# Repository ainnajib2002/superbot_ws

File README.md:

# 🛒 Semi-Autonomous Mobile Robot for Supermarket Shopping Efficiency

## 📌 Abstract
The rapid advancement of robotics has driven the emergence of innovative solutions to enhance the convenience and efficiency of supermarket shopping. This study presents the design of a prototype semi-autonomous mobile supermarket robot that integrates autonomous navigation, precise motor control, and intuitive human–robot interaction based on human following and hand gestures. The robot employs a configuration of two omnidirectional wheels and a caster wheel for balance, driven by PG45 DC motors controlled by an ESP32 microcontroller with a BTS7960 driver. A PI control system with parameters Kp = 0.1 and Ki = 0.004 maintains motor speed with a steady-state error below 5% and without significant overshoot, both under no-load and load conditions up to 30 kg. For navigation, the robot is equipped with an RPLiDAR A2 sensor, odometry, and mapping based on the SLAM Toolbox. Path planning is implemented using the A-Star algorithm and the Dynamic Window Approach (DWA). Experimental results demonstrate that the robot successfully completes multi-point navigation and avoids both static and dynamic obstacles, with an average response time of 3.51–6.52 seconds. Beyond navigation, the robot enables natural human interaction through an RGB camera processed with the YOLOv11-Pose deep learning model, achieving an F1-score above 0.92 and inference speed of 14 FPS. Distance estimation is performed using triangulation of head–neck keypoints, yielding an average accuracy of MAPE 5.3%. Hand gesture detection demonstrates high reliability with confidence scores above 0.83 at distances of 1.5–5 meters, allowing users to flexibly activate human-following mode or stop the robot. Tests conducted in a supermarket-like simulation environment confirm that the robot can stably follow users, maneuver in narrow aisles, and adaptively switch between operating modes. By combining precise motor control, SLAM-based navigation, and gesture-based interaction, this supermarket robot prototype shows strong potential as an intelligent solution to support a more ergonomic, efficient, and adaptive shopping experience. The perception system includes:

- **RGB Camera** → YOLOv11-Pose for human detection, pose estimation, and hand gesture recognition.
- **LiDAR (RPLiDAR A2)** → 2D mapping and obstacle detection.
- **Odometry (wheel encoders)** → position estimation.
- **Load Cell** → payload weight monitoring.

The navigation system uses **SLAM Toolbox** for mapping, **AMCL** for localization, and **Nav2** (A* for global path, DWA for local planner).

---

## ⚙️ System Architecture
The system is divided into modules connected via ROS 2 topics and services:

- **Perception**: RGB Camera + YOLOv11-Pose, LiDAR, Odometry.
- **Control**: Differential drive with omnidirectional wheels, ESP32 motor control, Load cell feedback.
- **Navigation**: SLAM Toolbox, AMCL, Nav2 (A*, DWA).
- **GUI**: Tkinter-based interface for product categories, teleoperation, and visualization in RViz.

---

## 🖼️ System 

### 🔧 Wheel System
|  |  |
|------------------------------------------------------------|----------------------------------------------------------------|

### 🗺️ Mapping & SLAM
|  |  |
|------------------------------------------------------------|----------------------------------------------------------------|

### 🖥️ GUI Interface & Gesture
|  |  |
|------------------------------------------------------------|----------------------------------------------------------------|

### 👀 Human Detection 
|  |  |
|-------------------------------------------------------------------------------------------------------------|------------------------------------------------------------------------------------------------------------------|

---

## 🎯 Methods

### 1. Hardware
- **Jetson Orin Nano / Xavier NX** → AI inference & high-level computation.
- **ESP32** → Low-level motor control, encoder feedback, load cell data.
- **DC Motors + Omnidirectional wheels** → Maneuverability in narrow aisles.
- **RPLiDAR A2** → 360° scanning.
- **RGB Camera** → Human & gesture detection.
- **Load Cell** → Payload monitoring.

### 2. Perception (YOLOv11-Pose)
- Detects **human**, **keypoints (head–neck)** for distance estimation, and **hand gestures**.
- Custom dataset: 6,650 images, classes = {person, rock, paper, scissors}.
- Training with transfer learning → converted to TensorRT engine for Jetson.
- FPS ≈ 14, F1-score ≈ 0.92.

### 3. Human Following & Gesture Control
- Hybrid tracking with **AprilTag + YOLOv11-Pose + Kalman Filter**.
- Distance estimation via vertical keypoint distance (head–neck triangulation).
- Hand gestures mapped to robot commands:
  - **Rock (✊)** → STOP
  - **Paper (✋)** → HUMAN FOLLOW
  - **Scissors (✌️)** → GO

### 4. Navigation
- **Mapping**: SLAM Toolbox (multi-session mapping, pose graph optimization).
- **Localization**: AMCL with adaptive particle filter.
- **Global Planner**: A* (efficient path planning).
- **Local Planner**: DWA (dynamic obstacle avoidance).

### 5. Load Cell Integration
- Measures payload weight in real-time.
- Publishes weight to GUI and ROS 2 topics.
- GUI indicator: color-coded status (safe, medium, overload).

---

## ▶️ Usage

### Build and Setup
```bash
# Clean build
rm -rf build/ install/ log/

# Build
colcon build --packages-select superbot_ws

# Source
source install/setup.bash
```

---

## 📍 Notes
- Nav2 tested with A* (global) + DWA (local). TEB considered but computationally heavier.
- Load cell integrated into GUI with reset function.
- SLAM Toolbox preferred over GMapping/Cartographer due to efficiency.

---

## 🤖 System Block Diagram

### 👀 System Block Diagram Robot
|  |
|---------------------------------------------------------------------------------------------------------------|

---

## 🔧 Installation & Setup
```bash
sudo apt install ros-foxy-tf2-tools
sudo apt install ros-foxy-robot-localization
sudo apt install ros-foxy-gazebo-ros-pkgs
sudo apt install ros-foxy-navigation2 ros-foxy-nav2-bringup ros-foxy-turtlebot3*
sudo apt install ros-foxy-ros2-control ros-foxy-ros2-controllers ros-foxy-gazebo-ros2-control
sudo apt install ros-foxy-xacro
sudo apt install ros-foxy-slam-toolbox
sudo apt install ros-foxy-twist-mux
sudo apt install joystick jstest-gtk evtest

pip install rplidar
pip install serial
```

- Install Arduino IDE & ESP32 package v2
- Reference: [Differential drive robot using ROS2 and ESP32](https://www.reddit.com/r/differential-drive-robot-using-ros2-and-esp32-aae289)
- Micro-ROS Serial Tutorial: [YouTube](https://www.youtube.com/watch?v=cLlK7uqFC2A)
- Motor controller demo: [YouTube](https://www.youtube.com/watch?v=-PCuDnpgiew)
- Hackster tutorial: [Hackster.io/amal-shaji](https://www.hackster.io/amal-shaji)

---

## 📖 References

[1] C. Thompson et al., "Changes to household food shopping practices during the COVID-19 restrictions: Evidence from the East of England," *Heal. Place*, vol. 78, no. July, p. 102906, 2022, doi: 10.1016/j.healthplace.2022.102906.

[2] S. Wang, Y. Ye, B. Ning, J. H. Cheah, and X. J. Lim, "Why Do Some Consumers Still Prefer In-Store Shopping? An Exploration of Online Shopping Cart Abandonment Behavior," *Front. Psychol.*, vol. 12, no. January, pp. 1–14, 2022, doi: 10.3389/fpsyg.2021.829696.

[3] H. Y. Purwantono, A. A. S. Gunawan, H. Tolle, M. Attamimi, and W. Budiharto, "A literature review: Feasibility Study of technology to improve shopping experience," *Procedia Comput. Sci.*, vol. 179, pp. 468–479, 2021, doi: 10.1016/j.procs.2021.01.030.

[4] D. L. M. Vikash Ranjan, Shafaq Akhtar, "Study on consumer satisfaction and loyalty towards," *Int. J. Adv. Multidiscip. Res.*, vol. 10, no. 1, pp. 89–99, 2023, doi: http://dx.doi.org/10.22192/ijamr.2023.10.01.009.

[5] A. Ramzan, R. Mustafa, Z. Rehman, S. Suleman, M. Noor, and R. Bibi, "Robotrolley: Customer Following Trolley (CFT)," *2023 17th Int. Conf. Open Source Syst. Technol. ICOSST 2023 - Proc.*, pp. 1–6, 2023, doi: 10.1109/ICOSST60641.2023.10414202.

[6] T. H. Tsai and C. H. Yao, "A robust tracking algorithm for a human-following mobile robot," *IET Image Process.*, vol. 15, no. 3, pp. 786–796, 2021, doi: 10.1049/ipr2.12062.

[7] G. C. Pătru, A. I. Pîrvan, D. Rosner, and R. V. Rughiniș, "Fiducial Marker Systems Overview and Empirical Analysis of Aruco, Apriltag and Cctag," *UPB Sci. Bull. Ser. C Electr. Eng. Comput. Sci.*, vol. 85, no. 2, pp. 49–62, 2023.

[8] D. Penaloza-Aponte et al., "Automated entrance monitoring to investigate honey bee foraging trips using open-source wireless platform and fiducial tags," *HardwareX*, vol. 20, no. November, p. e00609, 2024, doi: 10.1016/j.ohx.2024.e00609.

[9] A. Zachariae, F. Plahl, Y. Tang, I. Mamaev, B. Hein, and C. Wurll, "Human-robot interactions in autonomous hospital transports," *Rob. Auton. Syst.*, vol. 179, no. July, p. 104755, 2024, doi: 10.1016/j.robot.2024.104755.

[10] N. Reddy Kavya Sree, B. Anbarasu, and M. Luhitha, "Integration of LIDAR and Ultrasonic sensor for MAV collision avoidance," *ESIC 2025 - 5th Int. Conf. Emerg. Syst. Intell. Comput. Proc.*, pp. 832–836, 2025, doi: 10.1109/ESIC64052.2025.10962656.

[11] H. V. Pinnamaraju, P. R. Kapu, A. N. Juturu, and B. Anbarasu, "Distance Estimation for Collision Avoidance of Micro Aerial Vehicles using LiDAR Sensor," *Int. Conf. Autom. Comput. Renew. Syst. ICACRS 2022 - Proc.*, no. ICACRS, pp. 157–161, 2022, doi: 10.1109/ICACRS55517.2022.10029233.

[12] D. P. Suwandi, I. K. Wibowo, and M. M. Bachtiar, "Estimation of Ball Position Using Depth Camera for Middle Size Goalkeeper Robot," *IES 2022 - 2022 Int. Electron. Symp. Energy Dev. Clim. Chang. Solut. Clean Energy Transition, Proceeding*, pp. 374–379, 2022, doi: 10.1109/IES55876.2022.9888575.

[13] A. Mingozzi, A. Conti, F. Aleotti, M. Poggi, and S. Mattoccia, "Monitoring Social Distancing With Single Image Depth Estimation," *IEEE Trans. Emerg. Top. Comput. Intell.*, vol. 6, no. 6, pp. 1290–1301, 2022, doi: 10.1109/TETCI.2022.3171769.

[14] H. Herdianto, P. Sihombing, F. Fahmi, and T. Tulus, "Improving Object Distance Measurement Based on Mono Camera Using Magnification and Yolo Methods," *Int. Conf. Control Autom. Electron. Robot. Internet Things, Artif. Intell. CERIA 2024*, pp. 1–6, 2024, doi: 10.1109/CERIA64726.2024.10914711.

[15] Y. D. T. T. Wicaksana, A. Hendriawan, and N. Tamami, "Human Target Distance Estimation System Using Mono-camera On Human-Following Mobile Robot," *IES 2022 - 2022 Int. Electron. Symp. Energy Dev. Clim. Chang. Solut. Clean Energy Transition, Proceeding*, pp. 349–354, 2022, doi: 10.1109/IES55876.2022.9888331.

[16] T. Alhmiedat et al., "A SLAM-Based Localization and Navigation System for Social Robots: The Pepper Robot Case," *Machines*, vol. 11, no. 2, pp. 1–17, 2023, doi: 10.3390/machines11020158.

[17] G. Zhang, J. Yin, P. Deng, Y. Sun, L. Zhou, and K. Zhang, "Achieving Adaptive Visual Multi-Object Tracking with Unscented Kalman Filter," *Sensors*, vol. 22, no. 23, pp. 1–18, 2022, doi: 10.3390/s22239106.

[18] A. F. Rasheed and M. Zarkoosh, "YOLOv11 optimization for efficient resource utilization," *J. Supercomput.*, vol. 81, no. 9, 2025, doi: 10.1007/s11227-025-07520-3.

[19] L. Liu, A. Kurban, and Y. Liu, "Improved YOLOv11pose for Posture Estimation of Xinjiang Bactrian Camels," *Int. J. Adv. Comput. Sci. Appl.*, vol. 15, no. 12, pp. 364–371, 2024, doi: 10.14569/IJACSA.2024.0151239.

[20] M. Petković and I. Vujović, "Distance Estimation Approach for Maritime Traffic Surveillance Using Instance Segmentation," *J. Mar. Sci. Eng.*, vol. 12, no. 1, 2024, doi: 10.3390/jmse12010078.

[21] N. Herbaz, H. El Idrissi, and A. Badri, "Deep Learning Empowered Hand Gesture Recognition: using YOLO Techniques," *Proc. - SITA 2023 2023 14th Int. Conf. Intell. Syst. Theor. Appl.*, pp. 1–7, 2023, doi: 10.1109/SITA60746.2023.10373734.

[22] L. Zhou, C. Du, Z. Sun, T. L. Lam, and Y. Xu, "Long-Range Hand Gesture Recognition via Attention-based SSD Network," *Proc. - IEEE Int. Conf. Robot. Autom.*, vol. 2021-May, pp. 1832–1838, 2021, doi: 10.1109/ICRA48506.2021.9561189.

[23] L. Liu, D. Du, Y. Sun, and Y. Li, "SFMW-YOLO: A lightweight metal casting surface defect detection method based on modified YOLOv8s," *Expert Syst. Appl.*, vol. 287, no. May, p. 128170, 2025, doi: 10.1016/j.eswa.2025.128170.

[24] M. D. Islam et al., "Towards real-time weed detection and segmentation with lightweight CNN models on edge devices," *Comput. Electron. Agric.*, vol. 237, no. PB, p. 110600, 2025, doi: 10.1016/j.compag.2025.110600.

[25] S. Salimi, J. P. Queralta, and T. Westerlund, "Hyperledger Fabric Blockchain and ROS 2 Integration for Autonomous Mobile Robots," *2023 IEEE/SICE Int. Symp. Syst. Integr. SII 2023*, no. i, 2023, doi: 10.1109/SII55687.2023.10039326.

[26] P. A. Gutierrez-Flores and R. Bachmayer, "Concept development of a modular system for marine applications using ROS2 and micro-ROS," *2022 IEEE/OES Auton. Underw. Veh. Symp. AUV 2022*, 2022, doi: 10.1109/AUV53081.2022.9965867.

[27] H. Li et al., "Optimizing edge-enabled system for detecting green passion fruits in complex natural orchards using lightweight deep learning model," *Comput. Electron. Agric.*, vol. 234, no. March, p. 110269, 2025, doi: 10.1016/j.compag.2025.110269.

[28] S. Pan et al., "A lightweight robust RGB-T object tracker based on Jitter Factor and associated Kalman filter," *Inf. Fusion*, vol. 117, no. November 2024, p. 102842, 2025, doi: 10.1016/j.inffus.2024.102842.

[29] A. Kumar, R. Vohra, R. Jain, M. Li, C. Gan, and D. K. Jain, "Correlation filter based single object tracking: A review," *Inf. Fusion*, vol. 112, no. July, p. 102562, 2024, doi: 10.1016/j.inffus.2024.102562.

[30] S. Schramm, J. Rangel, D. A. Salazar, R. Schmoll, and A. Kroll, "Target Analysis for the Multispectral Geometric Calibration of Cameras in Visual and Infrared Spectral Range," *IEEE Sens. J.*, vol. 21, no. 2, pp. 2159–2168, 2021, doi: 10.1109/JSEN.2020.3019959.

[31] C. L. Shih, W. C. Huang, I. T. Anggraini, Y. Xiao, N. Funabiki, and C. P. Fan, "Performance Comparison between OpenPose and TRT-Pose for Self-Practice Yoga on Embedded GPU Platform," *2023 IEEE Int. Conf. Consum. Electron. ICCE-Asia 2023*, pp. 1–4, 2023, doi: 10.1109/ICCE-Asia59966.2023.10326363.

[32] J. Chen, S. Bai, G. Wan, Y. Li, J. Li, and Z. Cheng, "Research on defect detection method of automotive running lights based on keypoint identification," *Proc. 36th Chinese Control Decis. Conf. CCDC 2024*, pp. 5220–5225, 2024, doi: 10.1109/CCDC62350.2024.10588328.

[33] R. P. Duarte, C. A. Cunha, and J. C. Cardoso, "Automatic Camera Calibration Using a Single Image to extract Intrinsic and Extrinsic Parameters," *Orig. Res. Pap. Int. J. Intell. Syst. Appl. Eng. IJISAE*, vol. 2024, no. 3, pp. 1766–1778, 2024, [Online]. Available: www.ijisae.org

[34] T. H. Tsai and C. L. Lee, "Equipped with Monocular Depth Estimation and Intelligent Wake-Up Vision Based Tracking System for a Human-Following Mobile Robot," *2024 IEEE Int. Conf. Multimed. Expo Work. ICMEW 2024*, pp. 1–2, 2024, doi: 10.1109/ICMEW63481.2024.10645403.

[35] C. L. Yong, B. Hoe Kwan, D. W. K. Ng, and H. Seng Sim, "Human Tracking and Following using Machine Vision on a Mobile Service Robot," *2022 IEEE 10th Conf. Syst. Process Control. ICSPC 2022 - Proc.*, no. December, pp. 274–279, 2022, doi: 10.1109/ICSPC55597.2022.10001803.

[36] N. Van Toan, M. Do Hoang, P. B. Khoi, and S. Y. Yi, "The human-following strategy for mobile robots in mixed environments," *Rob. Auton. Syst.*, vol. 160, p. 104317, 2023, doi: 10.1016/j.robot.2022.104317.

[37] X. Zhang et al., "Image Recognition of Supermarket Shopping Robot Based on CNN," in *2020 IEEE International Conference on Artificial Intelligence and Computer Applications (ICAICA)*, pp. 1363–1368, 2020. doi: 10.1109/ICAICA50127.2020.9181936.

[38] Y. Li, Y. Chang, T. Yang, and Y. Li, "Understanding consumer responses to robot roles in human-robot service collaboration," *J. Retail. Consum. Serv.*, vol. 87, pp. 1–10, 2025, doi: 10.1016/j.jretconser.2025.104407.

[39] K. Zhu and T. Zhang, "Deep Reinforcement Learning Based Mobile Robot Navigation: A Review," *Tsinghua Sci. Technol.*, vol. 26, no. 5, pp. 674–691, 2021, doi: 10.26599/TST.2021.9010012.

[40] A. Candra, M. A. Budiman, and K. Hartanto, "Dijkstra's and A-Star in Finding the Shortest Path: A Tutorial," in *2020 International Conference on Data Science, Artificial Intelligence, and Business Analytics (DATABIA)*, pp. 28–32, 2020. doi: 10.1109/DATABIA50434.2020.9190342.

[41] D. Rachmawati and L. Gustin, "Analysis of Dijkstra's Algorithm and A∗ Algorithm in Shortest Path Problem," *J. Phys. Conf. Ser.*, vol. 1566, no. 1, pp. 1–7, 2020, doi: 10.1088/1742-6596/1566/1/012061.

[42] G. Tang, C. Tang, C. Claramunt, X. Hu, and P. Zhou, "Geometric A-Star Algorithm: An Improved A-Star Algorithm for AGV Path Planning in a Port Environment," *IEEE Access*, vol. 9, pp. 59196–59210, 2021, doi: 10.1109/ACCESS.2021.3070054.

[43] Y. Li, Z. Wang, and S. Zhang, "Path Planning of Robots Based on an Improved A-star Algorithm," *2022 IEEE 5th Adv. Inf. Manag. Commun. Electron. Autom. Control Conf.*, vol. 5, pp. 826–831, 2022, doi: 10.1109/IMCEC55388.2022.10019799.

[44] L. Zhang and Y. Li, "Mobile Robot Path Planning Algorithm Based on Improved A Star," in *Journal of Physics: Conference Series*, 2021. doi: 10.1088/1742-6596/1848/1/012013.

[45] S. Louda, N. Karkar, F. Seghir, and S. Refoufi, "Mobile Robot Path Planning Based on A-Star Algorithm and Artificial Potential Field Method for Autonomous Navigation," *2024 12th Int. Conf. Syst. Control. ICSC 2024*, pp. 441–446, 2024, doi: 10.1109/ICSC63929.2024.10928867.

[46] Y. Li et al., "A Review of Simultaneous Localization and Mapping Algorithms Based on Lidar," *World Electr. Veh. J.*, vol. 16, no. 2, pp. 1–29, 2025, doi: 10.3390/wevj16020056.

[47] J. Hernas and N. PiÃşrkowska, "Comparison of SLAM algorithms for autonomous navigation systems in ROS 2 environment: analysis of mapping accuracy, position estimation and resource consumption," *Authorea*, 2025, doi: 10.22541/au.175199254.49549720/v1.

[48] S. Macenski and I. Jambrecic, "SLAM Toolbox: SLAM for the Dynamic World," *J. Open Source Softw.*, vol. 6, no. 61, pp. 1–7, 2021, doi: 10.21105/joss.02783.

[49] Z. Zhang and G.-H. Yang, "Dynamic obstacle avoidance for car-like mobile robots based on neurodynamic optimization with control barrier functions," *Neurocomputing*, vol. 654, pp. 1–9, 2025, doi: 10.1016/j.neucom.2025.131252.

[50] C. Su, H. Wang, and C. Ko, "Development of an Autonomous Robot Replenishment System for Convenience Stores," 2023.

[51] Y. Zheng, J. Li, J. Deng, Y. Wang, J. Zhao, and J. Hou, "Research on Local Obstacle Avoidance of Power Inspection Robot Based on Improved TEB-DWA Algorithm," in *2025 5th International Conference on Electronic Technology, Communication and Information (ICETCI)*, IEEE, pp. 737–744, 2025. doi: 10.1109/icetci64844.2025.11084027.

[52] H. Yuan, H. Li, Y. Zhang, S. Du, L. Yu, and X. Wang, "Comparison and Improvement of Local Planners on ROS for Narrow Passages," *2022 Int. Conf. High Perform. Big Data Intell. Syst.*, pp. 125–130, 2022, doi: 10.1109/HDIS56859.2022.9991270.

[53] K. Gong, Z. Xu, and X. Zhang, "Bounded-DWA: An Efficient Local Planner for Ackermann-driven Vehicles on Sandy Terrain," in *2023 IEEE International Conference on Real-Time Computing and Robotics (RCAR)*, IEEE, pp. 632–637, 2023. doi: 10.1109/RCAR58764.2023.10249383.

[54] W. Huang and J. Yuan, "Improvements based on Adaptive Monte Carlo Localization," *2024 5th Int. Conf. Inf. Sci. Parallel Distrib. Syst.*, pp. 103–106, 2024, doi: 10.1109/ISPDS62779.2024.10667543.

[55] D. Ran, C. Huang, Y. Zhang, and W. Ren, "Fast relocation method for indoor mobile robots based on ORB feature matching," *2024 5th Int. Semin. Artif. Intell. Netw. Inf. Technol.*, pp. 64–70, 2024, doi: 10.1109/AINIT61980.2024.10581417.

[56] M.-A. Chung and C.-W. Lin, "An Improved Localization of Mobile Robotic System Based on AMCL Algorithm," *IEEE Sens. J.*, vol. 22, no. 1, pp. 900–908, 2022, doi: 10.1109/JSEN.2021.3126605.

[57] J. Xu, G. Liu, J. Liu, Z. Lv, and S. Gao, "EKF-Based Positioning Study of a Mobile Robot with McNamee Wheels," *J. Phys. Conf. Ser.*, vol. 2281, no. 1, pp. 1–9, 2022, doi: 10.1088/1742-6596/2281/1/012008.

[58] X. Wu, S. Yin, T. Chen, F. Wu, and Z. Huang, "Optimizing Cartographer for Indoor Mapping and Analysis," in *2025 6th International Conference on Computer Engineering and Application (ICCEA)*, pp. 1139–1143, 2025. doi: 10.1109/ICCEA65460.2025.11103219.

[59] O. O. Martins, A. A. Adekunle, O. M. Olaniyan, and B. O. Bolaji, "An Improved multi-objective a-star algorithm for path planning in a large workspace: Design, Implementation, and Evaluation," *Sci. African*, vol. 15, p. e01068, 2022, doi: 10.1016/j.sciaf.2021.e01068.

[60] R. Ni, J. Liu, H. Li, Z. Cao, X. Wang, and Y. Liu, "Research on Robot Path Planning Based on Fusion Algorithm of Optimized A∗ and DWA," in *2024 9th International Conference on Intelligent Computing and Signal Processing (ICSP)*, IEEE, pp. 1436–1439, 2024. doi: 10.1109/ICSP62122.2024.10743661.

[61] M. R. Imamoglu, E. Sumer, and H. Temeltas, "A Comparison of Local Planner Algorithms for a ROS-based Omnidirectional Mobile Robot," in *2023 8th International Conference on Robotics and Automation Engineering (ICRAE)*, IEEE, pp. 26–30, 2023. doi: 10.1109/ICRAE59816.2023.10458649.

[62] J. Palacín, E. Rubies, and E. Clotet, "Systematic Odometry Error Evaluation and Correction in a Human‐Sized Three‐Wheeled Omnidirectional Mobile Robot Using Flower‐Shaped Calibration Trajectories," *Appl. Sci.*, vol. 12, no. 5, pp. 1–23, 2022, doi: 10.3390/app12052606.

[63] G. L. Rezende, F. O. Silva, and L. S. Marques, "Comparison of Wheel Odometry and Visual Odometry for Low-Cost Vehicle Navigation," in *2024 Brazilian Symposium on Robotics (SBR) and 2024 Workshop on Robotics in Education (WRE)*, IEEE, pp. 91–96, 2024. doi: 10.1109/SBR/WRE63066.2024.10838039.

[64] A. de M. Gai, S. Bevilacqua, A. R. Cukla, and D. F. T. Gamarra, "Evaluation on IMU and odometry sensor fusion for a Turtlebot robot using AMCL on ROS framework," in *2023 Latin American Robotics Symposium (LARS), 2023 Brazilian Symposium on Robotics (SBR), and 2023 Workshop of Robotics in Education (WRE)*, IEEE, 2023, pp. 248–253. doi: 10.1109/LARS/SBR/WRE59448.2023.10332977.

[65] A. Barzegar, O. Doukhi, and D.-J. Lee, "Design and Implementation of an Autonomous Electric Vehicle for Self-Driving Control under GNSS-Denied Environments," *Appl. Scienses*, vol. 11, no. 8, pp. 1–23, 2021, doi: 10.3390/app11083688.

[66] I. Ullah, D. Adhikari, H. Khan, M. S. Anwar, S. Ahmad, and X. Bai, "Mobile robot localization: Current challenges and future prospective," *Comput. Sci. Rev.*, vol. 53, pp. 1–34, 2024, doi: 10.1016/j.cosrev.2024.100651.

[67] S. P. Chen, C. Y. Peng, G. S. Huang, C. C. Lai, C. C. Chen, and M. H. Yen, "Comparison of 2D and 3D LiDARs Trajectories and AMCL Positioning in ROS-Based move_base Navigation," in *2023 IEEE International Conference on Omni-Layer Intelligent Systems (COINS)*, IEEE, pp. 1–6, 2023. doi: 10.1109/COINS57856.2023.10189271.

[68] C. Jiang, C. Wang, and M. Wang, "Research on path planning for mobile robots based on improved A-star algorithm," in *2023 IEEE 7th Information Technology and Mechatronics Engineering Conference (ITOEC)*, IEEE, pp. 723–727, 2023. doi: 10.1109/ITOEC57671.2023.10292045.

[69] Y. Song and P. Ma, "Research on Mobile Robot Path Planning Based on Improved A-star Algorithm," in *2021 International Conference on Electronic Information Engineering and Computer Science (EIECS)*, IEEE, pp. 683–687, 2021. doi: 10.1109/EIECS53707.2021.9588002.

[70] Z. He, C. Liu, X. Chu, R. R. Negenborn, and Q. Wu, "Dynamic Anti-Collision A-Star Algorithm for Multi-Ship Encounter Situations," *Appl. Ocean Res.*, vol. 118, no. 1, pp. 2–26, 2022, doi: 10.1016/j.apor.2021.102995.

[71] H. Kuang, Y. Li, Y. Zhang, and Y. Feng, "Improved A-star Algorithm based on Topological Maps for Indoor Mobile Robot Path Planning," in *IEEE 6th Information Technology and Mechatronics Engineering Conference (ITOEC)*, IEEE, pp. 1236–1240, 2022. doi: 10.1109/ITOEC53115.2022.9734323.

[72] S. Guo, X. Pan, and Z. Liu, "AGV Path Planning Algorithm Based on Fusion of Improved A∗ and DWA," in *Proceedings of the 43rd Chinese Control Conference (CCC)*, Technical Committee on Control Theory, Chinese Association of Automation, pp. 1782–1787, 2024. doi: 10.23919/CCC63176.2024.10662786.

[73] Z. Lin and R. Taguchi, "Faster Implementation of The Dynamic Window Approach Based on Non-Discrete Path Representation," *Math. Artic.*, vol. 11, no. 21, pp. 1–20, 2023, doi: doi.org/10.3390/math11214424.

[74] S. M. Sakti, A. D. Laksito, B. W. Sari, and D. Prabowo, "Music Recommendation System Using Content-based Filtering Method with Euclidean Distance Algorithm," in *2022 6th International Conference on Information Technology, Information Systems and Electrical Engineering (ICITISEE)*, IEEE, pp. 385–390, 2022. doi: 10.1109/ICITISEE57756.2022.10057753.

[75] R. Mussabayev, "Optimizing Euclidean Distance Computation," *Mathematics*, vol. 12, no. 23, pp. 1–36, 2024, doi: 10.3390/math12233787.

[76] X. Li, X. Hu, Z. Wang, and Z. Du, "Path planning based on combination of improved A-STAR Algorithm and DWA algorithm," *Proc. - 2020 2nd Int. Conf. Artif. Intell. Adv. Manuf. AIAM 2020*, no. 1, pp. 99–103, 2020, doi: 10.1109/AIAM50918.2020.00025.

[77] P. Li, L. Hao, Y. Zhao, and J. Lu, "Robot obstacle avoidance optimization by A* and DWA fusion algorithm," *PLoS One*, vol. 19, no. 4 April, pp. 1–21, 2024, doi: 10.1371/journal.pone.0302026.

[78] D. Wang, J. Zhang, and W. Wang, "A Conflict Resolution Method for Multi-Robot Path Planning Based on an Improved Variable-Weight Dynamic Window Approach," *2025 17th Int. Conf. Adv. Comput. Intell.*, no. Icaci, pp. 107–112, 2025, doi: 10.1109/icaci65340.2025.11096346.

[79] B. Hahn, "Enhancing Obstacle Avoidance in Dynamic Window Approach via Dynamic Obstacle Behavior Prediction," *Actuators*, vol. 14, no. 5, 2025, doi: 10.3390/act14050207.

[80] C. Xu, J. Park, and J. C. Lee, "The effect of shopping channel (online vs offline) on consumer decision process and firm's marketing strategy," *Internet Res.*, vol. 32, no. 3, pp. 971–987, 2022, doi:

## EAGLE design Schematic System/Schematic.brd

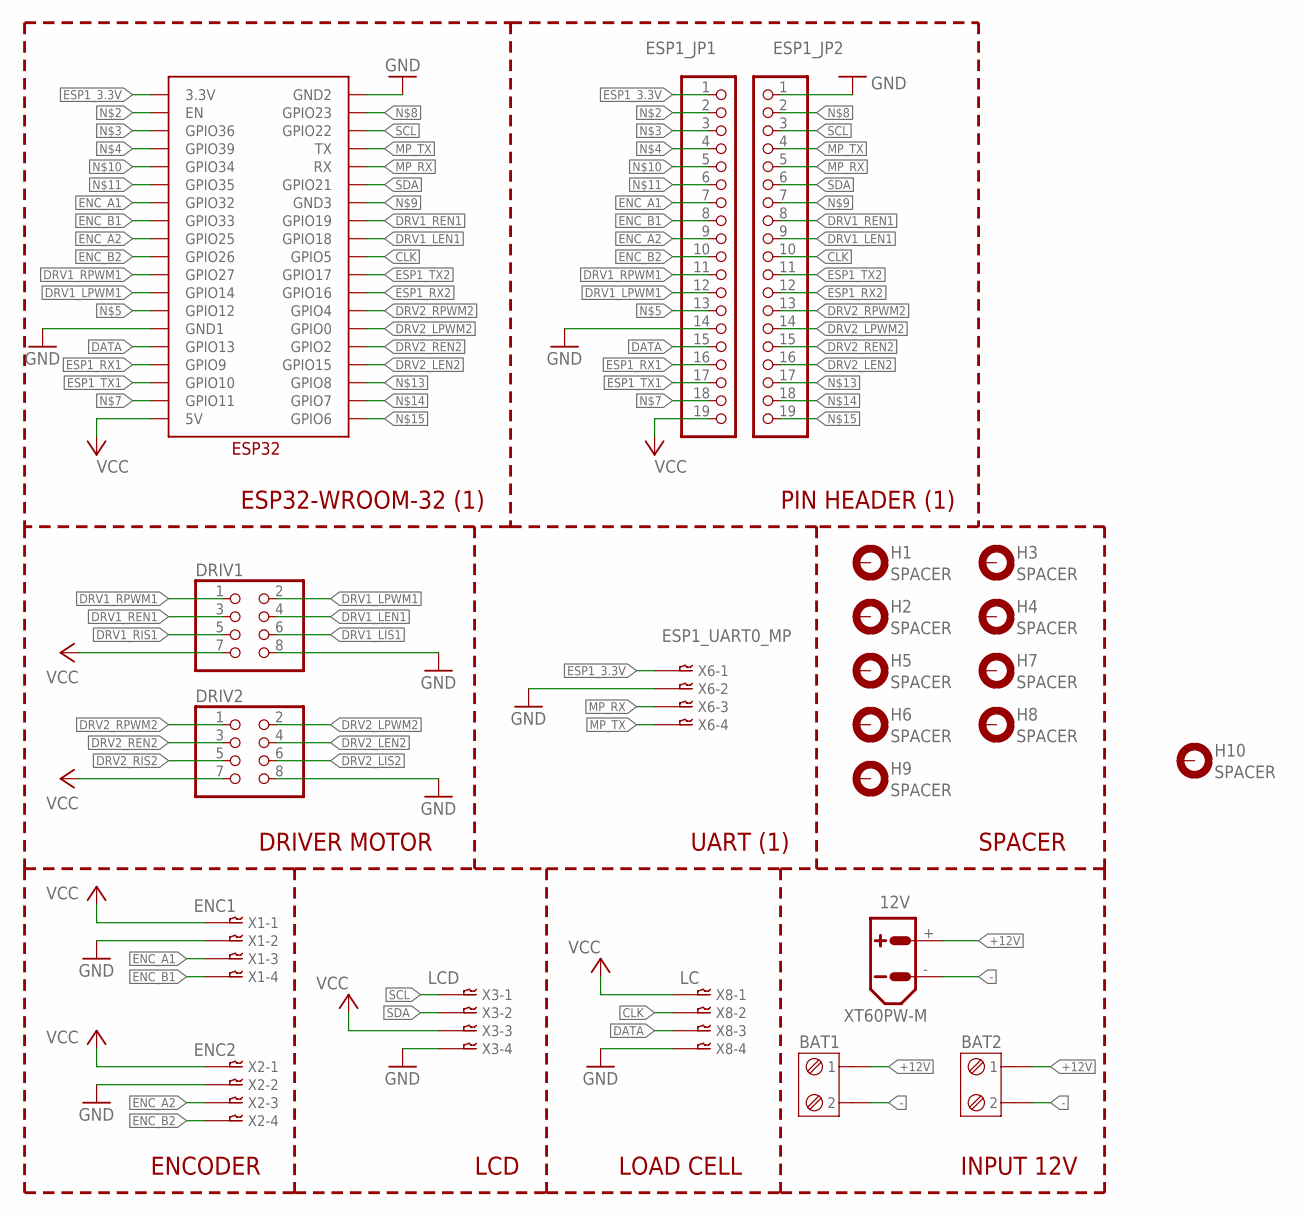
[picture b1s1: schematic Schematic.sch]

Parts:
12V: XT60PW-M
BAT1, BAT2: TERMINAL-BLOK-2P; TERMINAL_BLOK_2P
DRIV1, DRIV2: PINHD-2X4; 2X04
ESP1_JP1, ESP1_JP2: PINHD-1X19; 1X19
H1, H2, H3, H4, H5, H6, H7, H8, H9, H10: SPACER; 3,0-PAD
U$1: ESP32_GRBL
X1: ENC1; B4B-XH
X2: ENC2; B4B-XH
X3: LCD; B4B-XH
X6: ESP1_UART0_MP; B4B-XH
X8: LC; B4B-XH

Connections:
+12V: 12V.+, BAT1.1, BAT2.1
-: 12V.-, BAT1.2, BAT2.2
CLK: ESP1_JP2.10, U$1.GPIO5, X8.P$2
DATA: ESP1_JP1.15, U$1.GPIO13, X8.P$3
DRV1_LEN1: DRIV1.4, ESP1_JP2.9, U$1.GPIO18
DRV1_LIS1: DRIV1.6
DRV1_LPWM1: DRIV1.2, ESP1_JP1.12, U$1.GPIO14
DRV1_REN1: DRIV1.3, ESP1_JP2.8, U$1.GPIO19
DRV1_RIS1: DRIV1.5
DRV1_RPWM1: DRIV1.1, ESP1_JP1.11, U$1.GPIO27
DRV2_LEN2: DRIV2.4, ESP1_JP2.16, U$1.GPIO15
DRV2_LIS2: DRIV2.6
DRV2_LPWM2: DRIV2.2, ESP1_JP2.14, U$1.GPIO0
DRV2_REN2: DRIV2.3, ESP1_JP2.15, U$1.GPIO2
DRV2_RIS2: DRIV2.5
DRV2_RPWM2: DRIV2.1, ESP1_JP2.13, U$1.GPIO4
ENC_A1: ESP1_JP1.7, U$1.GPIO32, X1.P$3
ENC_A2: ESP1_JP1.9, U$1.GPIO25, X2.P$3
ENC_B1: ESP1_JP1.8, U$1.GPIO33, X1.P$4
ENC_B2: ESP1_JP1.10, U$1.GPIO26, X2.P$4
ESP1_3.3V: ESP1_JP1.1, U$1.3.3V, X6.P$1
ESP1_RX1: ESP1_JP1.16, U$1.GPIO9
ESP1_RX2: ESP1_JP2.12, U$1.GPIO16
ESP1_TX1: ESP1_JP1.17, U$1.GPIO10
ESP1_TX2: ESP1_JP2.11, U$1.GPIO17
GND: DRIV1.8, DRIV2.8, ESP1_JP1.14, ESP1_JP2.1, U$1.GND1, U$1.GND2, X1.P$2, X2.P$2, X3.P$4, X6.P$2, X8.P$4
MP_RX: ESP1_JP2.5, U$1.RX, X6.P$3
MP_TX: ESP1_JP2.4, U$1.TX, X6.P$4
unnamed: ESP1_JP1.2, U$1.EN
unnamed: ESP1_JP1.3, U$1.GPIO36
unnamed: ESP1_JP1.4, U$1.GPIO39
unnamed: ESP1_JP1.13, U$1.GPIO12
unnamed: ESP1_JP1.18, U$1.GPIO11
unnamed: ESP1_JP2.2, U$1.GPIO23
unnamed: ESP1_JP2.7, U$1.GND3
unnamed: ESP1_JP1.5, U$1.GPIO34
unnamed: ESP1_JP1.6, U$1.GPIO35
unnamed: ESP1_JP2.17, U$1.GPIO8
unnamed: ESP1_JP2.18, U$1.GPIO7
unnamed: ESP1_JP2.19, U$1.GPIO6
SCL: ESP1_JP2.3, U$1.GPIO22, X3.P$1
SDA: ESP1_JP2.6, U$1.GPIO21, X3.P$2
VCC: DRIV1.7, DRIV2.7, ESP1_JP1.19, U$1.5V, X1.P$1, X2.P$1, X3.P$3, X8.P$1

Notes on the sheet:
ESP32-WROOM-32 (1)
PIN HEADER (1)
DRIVER MOTOR
UART (1)
SPACER
INPUT 12V
ENCODER
LCD
LOAD CELL

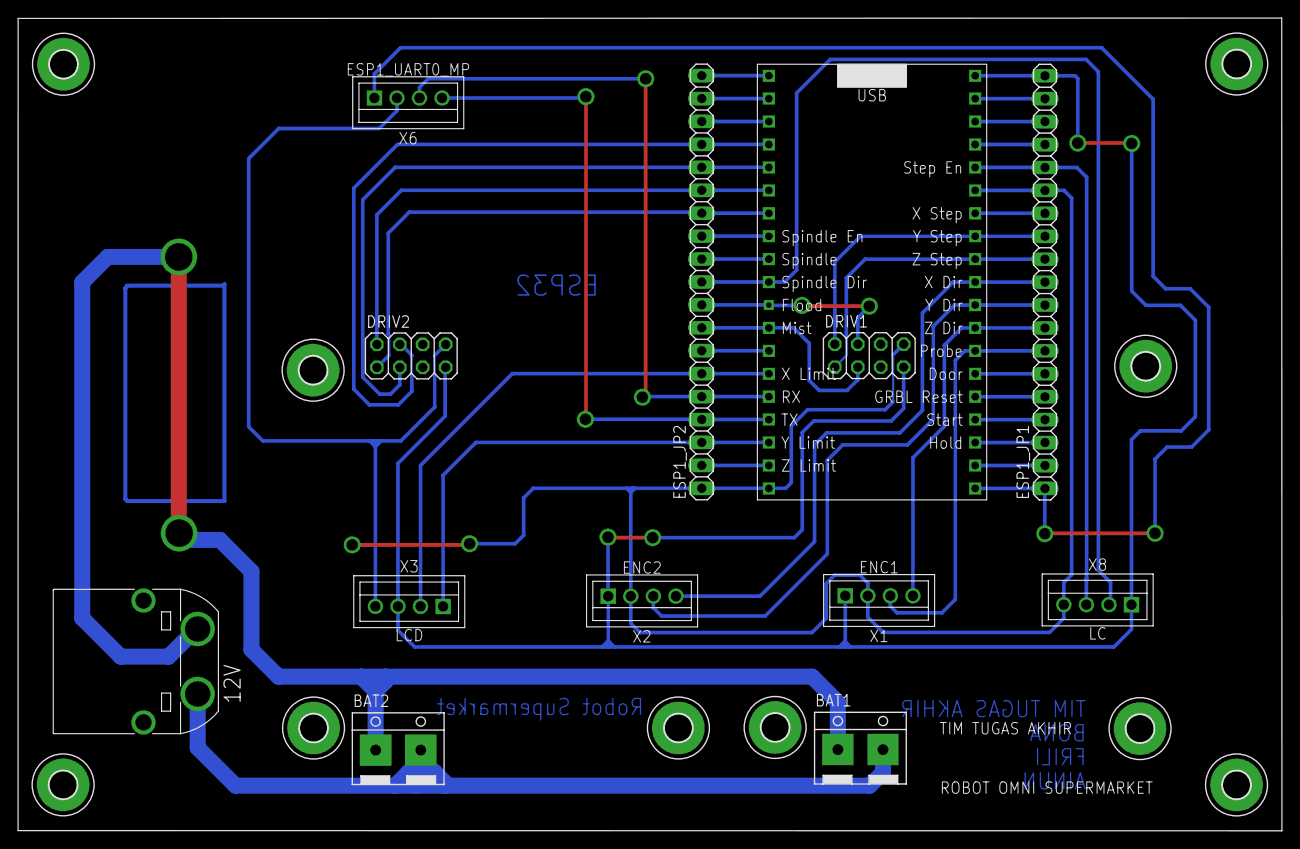
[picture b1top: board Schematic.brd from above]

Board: 2 copper layers, 140.0 x 90.0 mm, 23 parts (0 on the bottom side), 39 nets.

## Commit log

2025-08-29 Add src folder of superbot_ws
2025-08-29 Update README.md
    edit some change and notes
2025-08-29 Update README.md
    edit some
2025-08-29 Update requirements.txt
    add appriltag and kalman filter
2025-08-29 add navigation2 custom
2025-08-29 Remove old submodule references
2025-08-29 Add costmap_converter and teb_local_planner as submodules
